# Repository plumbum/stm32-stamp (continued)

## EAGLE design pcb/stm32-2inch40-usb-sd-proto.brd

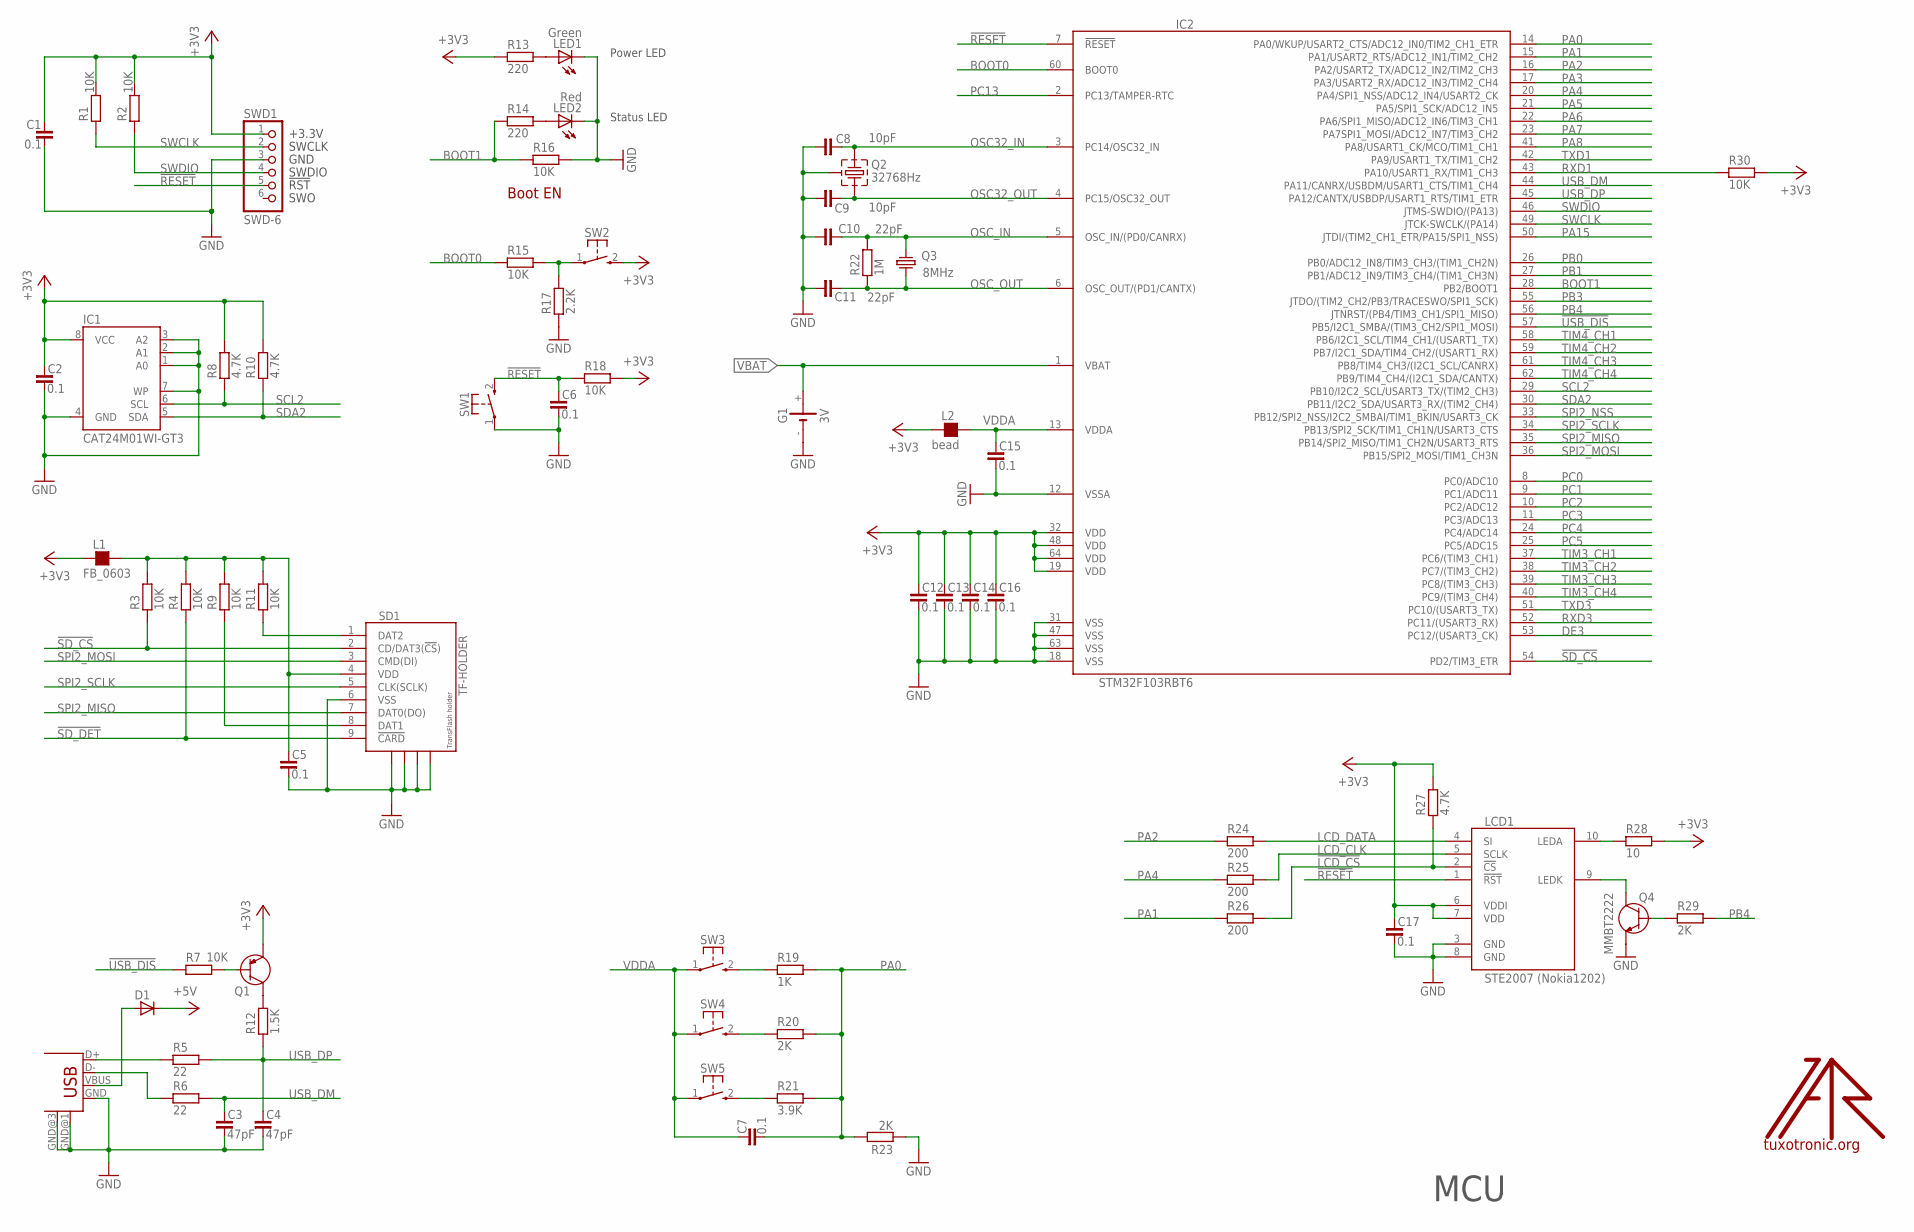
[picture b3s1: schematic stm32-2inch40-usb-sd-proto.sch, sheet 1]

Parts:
C1, C2, C5, C6, C7, C12, C13, C14, C15, C16, C17: 0.1; C0603
C3, C4: 47pF; C0603
C8, C9: 10pF; C0603
C10, C11: 22pF; C0603
D1: D-SOD-87; SOD87
G1: 3V; SMT1220
IC1: CAT24M01WI-GT3; SO08
IC2: STM32F103RBT6; TQFP64
L1: FB_0603; L0603
L2: bead; L0603
LCD1: STE2007 (Nokia1202); NOKIA1202LCD-EXT
LED1: Green; CHIP-LED0805
LED2: Red; CHIP-LED0805
LOGO1: LOGO; TT_LOGO
Q1: PNP-SOT23; SOT23
Q2: 32768Hz; TC38H-G
Q3: 8MHz; HC49/S
Q4: MMBT2222; SOT23
R1, R2, R3, R4, R7, R9, R11, R15, R16, R18, R30: 10K; R0603
R5, R6: 22; R0603
R8, R10, R27: 4.7K; R0603
R12: 1.5K; R0603
R13, R14: 220; R0603
R17: 2.2K; R0603
R19: 1K; R0603
R20, R23, R29: 2K; R0603
R21: 3.9K; R0603
R22: 1M; R0603
R24, R25, R26: 200; R0603
R28: 10; R0603
SD1: TF-HOLDER; TF-PULL
SW1, SW2, SW3, SW4, SW5: KSS-2EG4430
SWD1: SWD-6; JTAG6PIN
USB1: USB-MB-S

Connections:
!LCD_CS: LCD1.2 (!CS), R26.2, R27.1
!RESET: C6.1, IC2.7 (!RESET), LCD1.1 (!RST), R18.1, SW1.2 (S), SWD1.5
!SD_CS: IC2.54 (PD2/TIM3_ETR), R3.1, SD1.2 (CD/DAT3(!CS!))
!SD_DET: R4.1, SD1.9 (!CARD)
!USB_DIS: IC2.57 (PB5/I2C1_SMBA/(TIM3_CH2/SPI1_MOSI)), R7.1
+3V3: C1.1, C2.1, C12.1, C13.1, C14.1, C16.1, C17.1, IC1.8 (VCC), IC2.19 (VDD), IC2.32 (VDD), IC2.48 (VDD), IC2.64 (VDD), L1.1, L2.1, LCD1.6 (VDDI), LCD1.7 (VDD), Q1.2 (E), R1.2, R2.2, R8.2, R10.2, R13.1, R18.2, R27.2, R28.2, R30.2, SW2.2 (S), SWD1.1; also elsewhere on the board
+5V: D1.1 (C); also elsewhere on the board
BOOT0: IC2.60 (BOOT0), R15.1
BOOT1: IC2.28 (PB2/BOOT1), R14.1, R16.1
DE3: IC2.53 (PC12/(USART3_CK)); also elsewhere on the board
GND: C1.2, C2.2, C3.2, C4.2, C5.2, C6.2, C8.2, C9.2, C10.2, C11.2, C12.2, C13.2, C14.2, C15.2, C16.2, C17.2, G1.-, IC1.1 (A0), IC1.2 (A1), IC1.3 (A2), IC1.4 (GND), IC1.7 (WP), IC2.12 (VSSA), IC2.18 (VSS), IC2.31 (VSS), IC2.47 (VSS), IC2.63 (VSS), LCD1.3 (GND), LCD1.8 (GND), LED1.C, LED2.C, Q2.GND, Q4.2 (E), R16.2, R17.1, R23.1, SD1.6 (VSS), SD1.S1, SD1.S2, SD1.S3, SD1.S4, SW1.1, SWD1.3, USB1.GND, USB1.GND@1 (GND), USB1.GND@3 (GND); also elsewhere on the board
LCD_CLK: LCD1.5 (SCLK), R25.2
LCD_DATA: LCD1.4 (SI), R24.2
unnamed: Q1.3 (C), R12.2
unnamed: D1.2 (A), USB1.VBUS
unnamed: R15.2, R17.2, SW2.1
unnamed: C5.1, L1.2, R3.2, R4.2, R9.2, R11.2, SD1.4 (VDD)
unnamed: R11.1, SD1.1 (DAT2)
unnamed: R9.1, SD1.8 (DAT1)
unnamed: R5.1, USB1.D+
unnamed: LED1.A, R13.2
unnamed: LCD1.9 (LEDK), Q4.3 (C)
unnamed: LED2.A, R14.2
unnamed: LCD1.10 (LEDA), R28.1
unnamed: Q4.1 (B), R29.1
unnamed: R19.1, SW3.2 (S)
unnamed: R20.1, SW4.2 (S)
unnamed: R21.1, SW5.2 (S)
unnamed: R6.1, USB1.D-
unnamed: Q1.1 (B), R7.2
OSC32_IN: C8.1, IC2.3 (PC14/OSC32_IN), Q2.2
OSC32_OUT: C9.1, IC2.4 (PC15/OSC32_OUT), Q2.1
OSC_IN: C10.1, IC2.5 (OSC_IN/(PD0/CANRX)), Q3.1, R22.2
OSC_OUT: C11.1, IC2.6 (OSC_OUT/(PD1/CANTX)), Q3.2, R22.1
PA0: C7.2, IC2.14 (PA0/WKUP/USART2_CTS/ADC12_IN0/TIM2_CH1_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), R19.2, R20.2, R21.2, R23.2; also elsewhere on the board
PA1: IC2.15 (PA1/USART2_RTS/ADC12_IN1/TIM2_CH2), R26.1; also elsewhere on the board
PA2: IC2.16 (PA2/USART2_TX/ADC12_IN2/TIM2_CH3), R24.1; also elsewhere on the board
PA3: IC2.17 (PA3/USART2_RX/ADC12_IN3/TIM2_CH4); also elsewhere on the board
PA4: IC2.20 (PA4/SPI1_NSS/ADC12_IN4/USART2_CK), R25.1; also elsewhere on the board
PA5: IC2.21 (PA5/SPI1_SCK/ADC12_IN5); also elsewhere on the board
PA6: IC2.22 (PA6/SPI1_MISO/ADC12_IN6/TIM3_CH1); also elsewhere on the board
PA7: IC2.23 (PA7SPI1_MOSI/ADC12_IN7/TIM3_CH2); also elsewhere on the board
PA8: IC2.41 (PA8/USART1_CK/MCO/TIM1_CH1); also elsewhere on the board
PA15: IC2.50 (JTDI/(TIM2_CH1_ETR/PA15/SPI1_NSS)); also elsewhere on the board
PB0: IC2.26 (PB0/ADC12_IN8/TIM3_CH3/(TIM1_CH2N)); also elsewhere on the board
PB1: IC2.27 (PB1/ADC12_IN9/TIM3_CH4/(TIM1_CH3N)); also elsewhere on the board
PB3: IC2.55 (JTDO/(TIM2_CH2/PB3/TRACESWO/SPI1_SCK)); also elsewhere on the board
PB4: IC2.56 (JTNRST/(PB4/TIM3_CH1/SPI1_MISO)), R29.2
PC0: IC2.8 (PC0/ADC10); also elsewhere on the board
PC1: IC2.9 (PC1/ADC11); also elsewhere on the board
PC2: IC2.10 (PC2/ADC12); also elsewhere on the board
PC3: IC2.11 (PC3/ADC13); also elsewhere on the board
PC4: IC2.24 (PC4/ADC14); also elsewhere on the board
PC5: IC2.25 (PC5/ADC15); also elsewhere on the board
PC13: IC2.2 (PC13/TAMPER-RTC); also elsewhere on the board
RXD1: IC2.43 (PA10/USART1_RX/TIM1_CH3), R30.1; also elsewhere on the board
RXD3: IC2.52 (PC11/(USART3_RX)); also elsewhere on the board
SCL2: IC1.6 (SCL), IC2.29 (PB10/I2C2_SCL/USART3_TX/(TIM2_CH3)), R8.1; also elsewhere on the board
SDA2: IC1.5 (SDA), IC2.30 (PB11/I2C2_SDA/USART3_RX/(TIM2_CH4)), R10.1; also elsewhere on the board
SPI2_MISO: IC2.35 (PB14/SPI2_MISO/TIM1_CH2N/USART3_RTS), SD1.7 (DAT0(DO)); also elsewhere on the board
SPI2_MOSI: IC2.36 (PB15/SPI2_MOSI/TIM1_CH3N), SD1.3 (CMD(DI)); also elsewhere on the board
SPI2_NSS: IC2.33 (PB12/SPI2_NSS/I2C2_SMBAI/TIM1_BKIN/USAR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); also elsewhere on the board
SPI2_SCLK: IC2.34 (PB13/SPI2_SCK/TIM1_CH1N/USART3_CTS), SD1.5 (CLK(SCLK)); also elsewhere on the board
SWCLK: IC2.49 (JTCK-SWCLK/(PA14)), R1.1, SWD1.2
SWDIO: IC2.46 (JTMS-SWDIO/(PA13)), R2.1, SWD1.4
TIM3_CH1: IC2.37 (PC6/(TIM3_CH1)); also elsewhere on the board
TIM3_CH2: IC2.38 (PC7/(TIM3_CH2)); also elsewhere on the board
TIM3_CH3: IC2.39 (PC8/(TIM3_CH3)); also elsewhere on the board
TIM3_CH4: IC2.40 (PC9/(TIM3_CH4)); also elsewhere on the board
TIM4_CH1: IC2.58 (PB6/I2C1_SCL/TIM4_CH1/(USART1_TX)); also elsewhere on the board
TIM4_CH2: IC2.59 (PB7/I2C1_SDA/TIM4_CH2/(USART1_RX)); also elsewhere on the board
TIM4_CH3: IC2.61 (PB8/TIM4_CH3/(I2C1_SCL/CANRX)); also elsewhere on the board
TIM4_CH4: IC2.62 (PB9/TIM4_CH4/(I2C1_SDA/CANTX)); also elsewhere on the board
TXD1: IC2.42 (PA9/USART1_TX/TIM1_CH2); also elsewhere on the board
TXD3: IC2.51 (PC10/(USART3_TX)); also elsewhere on the board
USB_DM: C3.1, IC2.44 (PA11/CANRX/USBDM/USART1_CTS/TIM1_CH4), R6.2
USB_DP: C4.1, IC2.45 (PA12/CANTX/USBDP/USART1_RTS/TIM1_ETR), R5.2, R12.1
VBAT: G1.+, IC2.1 (VBAT)
VDDA: C7.1, C15.1, IC2.13 (VDDA), L2.2, SW3.1, SW4.1, SW5.1

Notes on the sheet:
Boot EN
Status LED
MCU
Power LED

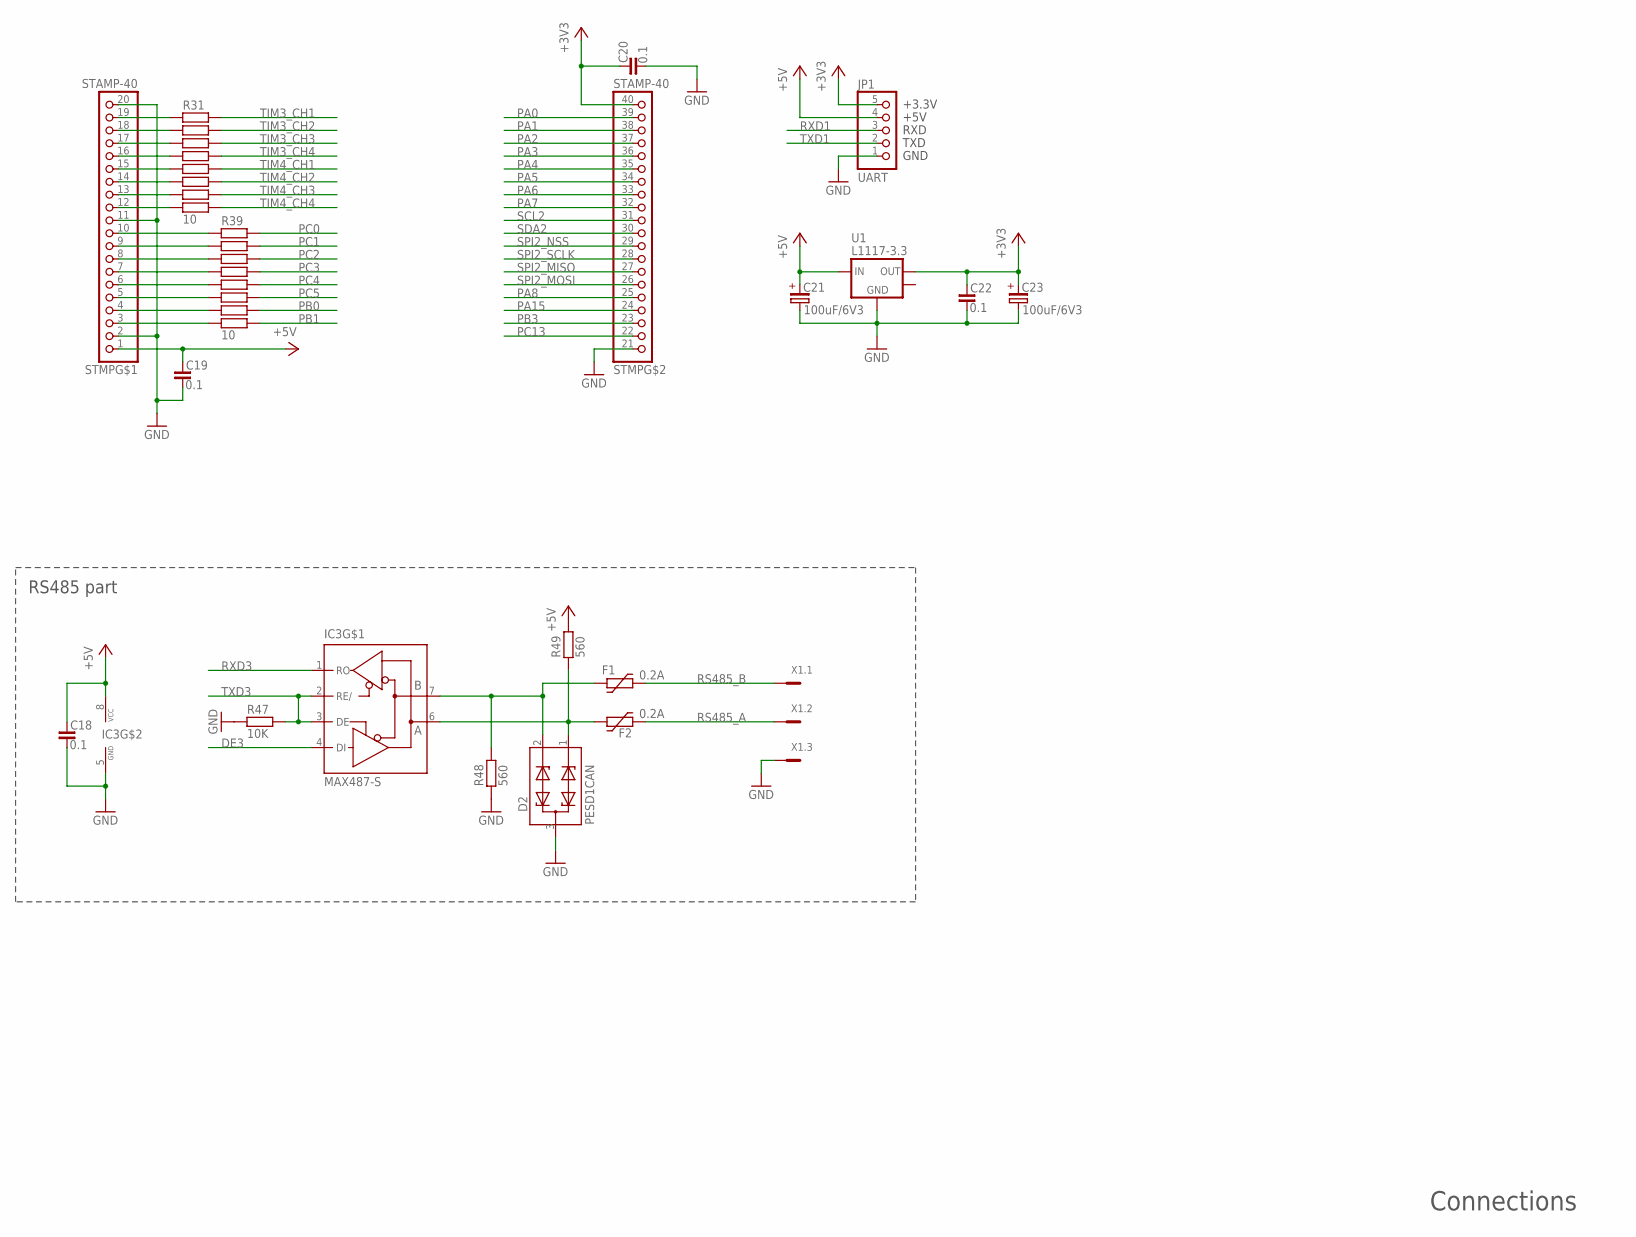
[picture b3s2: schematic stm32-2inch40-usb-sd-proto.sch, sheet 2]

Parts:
C18: 0.1; C0603
C19, C20, C22: 0.1; C0805
C21, C23: 100uF/6V3; SMC_D
D2: PESD1CAN; SOT23
F1, F2: 0.2A; 1206L
IC3: MAX487-S; SO08
JP1: UART; UART_1X05
R31, R32, R33, R34, R35, R36, R37, R38, R39, R40, R41, R42, R43, R44, R45, R46: 10; R0603
R47: 10K; R0603
R48, R49: 560; R0603
STMP: STAMP-40
U1: L1117-3.3; SOT223
X1: MCV3

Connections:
+3V3: C20.1, C22.1, C23.+, JP1.5, STMP.40 (20), U1.2 (OUT); also elsewhere on the board
+5V: C18.1, C19.1, C21.+, IC3.8 (VCC), JP1.4, R49.2, STMP.1, U1.3 (IN); also elsewhere on the board
DE3: IC3.4 (DI); also elsewhere on the board
GND: C18.2, C19.2, C20.2, C21.-, C22.2, C23.-, D2.3, IC3.5 (GND), JP1.1, R47.1, R48.1, STMP.2, STMP.11, STMP.20, STMP.21 (1), U1.1 (GND), X1.3; also elsewhere on the board
unnamed: D2.2, F1.P$1 (1), IC3.7 (B), R48.2
unnamed: R39.1, STMP.10
unnamed: R40.1, STMP.9
unnamed: R31.1, STMP.19
unnamed: R32.1, STMP.18
unnamed: R33.1, STMP.17
unnamed: R34.1, STMP.16
unnamed: R35.1, STMP.15
unnamed: R36.1, STMP.14
unnamed: R37.1, STMP.13
unnamed: R38.1, STMP.12
unnamed: R41.1, STMP.8
unnamed: R42.1, STMP.7
unnamed: R43.1, STMP.6
unnamed: R44.1, STMP.5
unnamed: R45.1, STMP.4
unnamed: R46.1, STMP.3
unnamed: D2.1, F2.P$1 (1), IC3.6 (A), R49.1
PA0: STMP.39 (19); also elsewhere on the board
PA1: STMP.38 (18); also elsewhere on the board
PA2: STMP.37 (17); also elsewhere on the board
PA3: STMP.36 (16); also elsewhere on the board
PA4: STMP.35 (15); also elsewhere on the board
PA5: STMP.34 (14); also elsewhere on the board
PA6: STMP.33 (13); also elsewhere on the board
PA7: STMP.32 (12); also elsewhere on the board
PA8: STMP.25 (5); also elsewhere on the board
PA15: STMP.24 (4); also elsewhere on the board
PB0: R45.2; also elsewhere on the board
PB1: R46.2; also elsewhere on the board
PB3: STMP.23 (3); also elsewhere on the board
PC0: R39.2; also elsewhere on the board
PC1: R40.2; also elsewhere on the board
PC2: R41.2; also elsewhere on the board
PC3: R42.2; also elsewhere on the board
PC4: R43.2; also elsewhere on the board
PC5: R44.2; also elsewhere on the board
PC13: STMP.22 (2); also elsewhere on the board
RS485_A: F2.P$2 (2), X1.2
RS485_B: F1.P$2 (2), X1.1
RXD1: JP1.3; also elsewhere on the board
RXD3: IC3.1 (RO); also elsewhere on the board
SCL2: STMP.31 (11); also elsewhere on the board
SDA2: STMP.30 (10); also elsewhere on the board
SPI2_MISO: STMP.27 (7); also elsewhere on the board
SPI2_MOSI: STMP.26 (6); also elsewhere on the board
SPI2_NSS: STMP.29 (9); also elsewhere on the board
SPI2_SCLK: STMP.28 (8); also elsewhere on the board
TIM3_CH1: R31.2; also elsewhere on the board
TIM3_CH2: R32.2; also elsewhere on the board
TIM3_CH3: R33.2; also elsewhere on the board
TIM3_CH4: R34.2; also elsewhere on the board
TIM4_CH1: R35.2; also elsewhere on the board
TIM4_CH2: R36.2; also elsewhere on the board
TIM4_CH3: R37.2; also elsewhere on the board
TIM4_CH4: R38.2; also elsewhere on the board
TXD1: JP1.2; also elsewhere on the board
TXD3: IC3.2 (RE/), IC3.3 (DE), R47.2; also elsewhere on the board

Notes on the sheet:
Connections
RS485 part

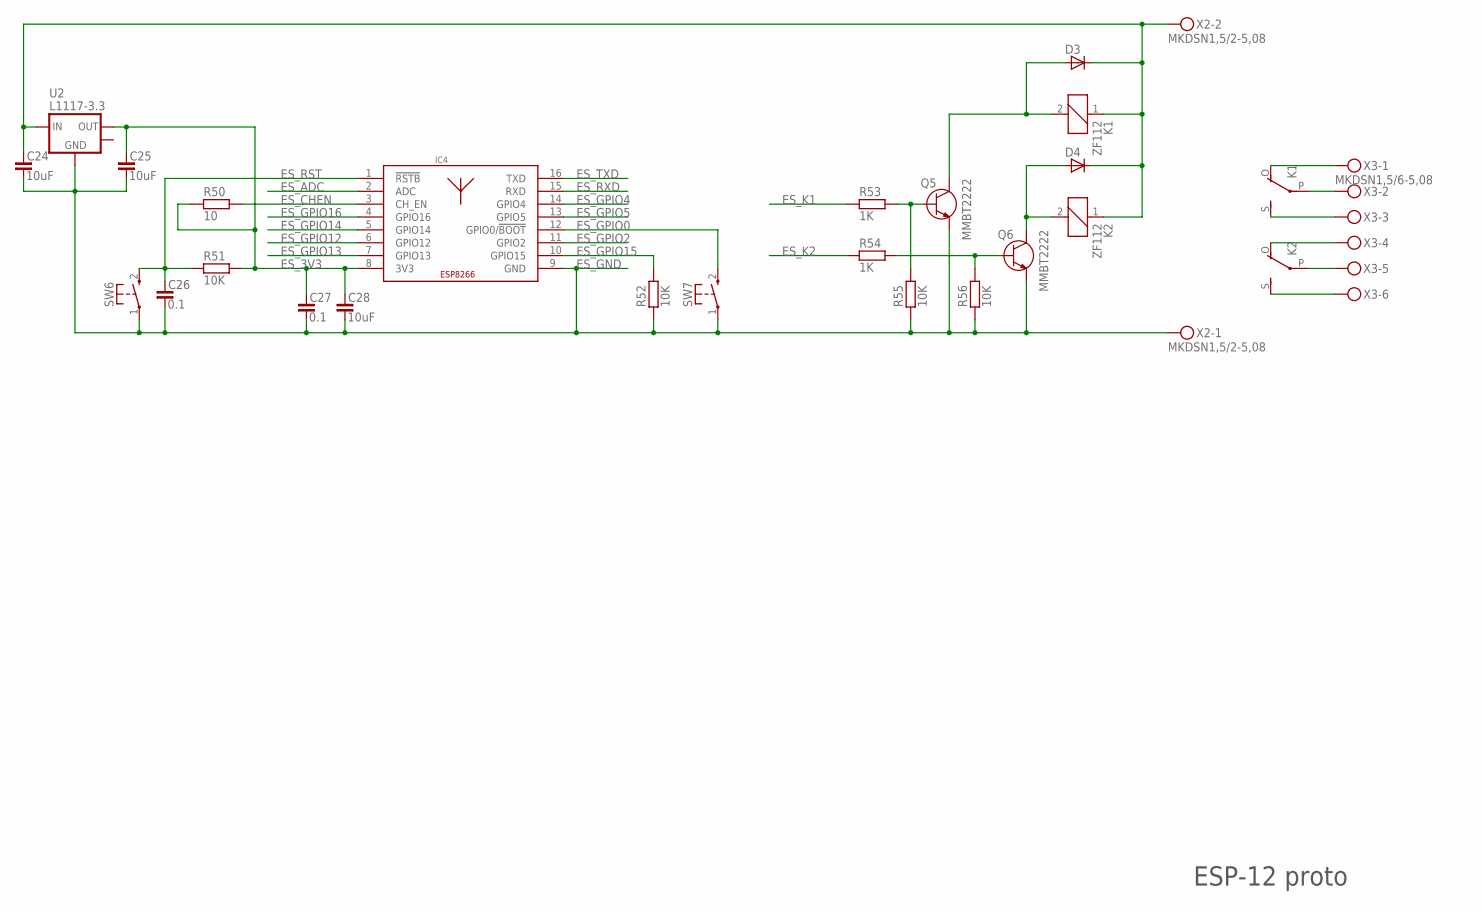
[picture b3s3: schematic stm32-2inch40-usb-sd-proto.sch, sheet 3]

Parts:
C24, C25, C28: 10uF; C0805
C26, C27: 0.1; C0805
D3, D4: D-SOD-80; SOD80
IC4: ESP-12; ESP12
K1, K2: ZF112
Q5, Q6: MMBT2222; SOT23
R50: 10; R0805
R51, R52, R55, R56: 10K; R0805
R53, R54: 1K; R0805
SW6, SW7: KSS-2EG4430
U2: L1117-3.3; SOT223
X2: MKDSN1,5/2-5,08
X3: MKDSN1,5/6-5,08

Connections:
+5V1: C24.1, D3.1 (C), D4.1 (C), K1.1, K2.1, U2.3 (IN), X2.2
ES_3V3: C25.1, C27.1, C28.1, IC4.8 (3V3), R50.1, R51.2, U2.2 (OUT)
ES_ADC: IC4.2 (ADC)
ES_CHEN: IC4.3 (CH_EN), R50.2
ES_GND: C24.2, C25.2, C26.2, C27.2, C28.2, IC4.9 (GND), Q5.2 (E), Q6.2 (E), R52.1, R55.1, R56.1, SW6.1, SW7.1, U2.1 (GND), X2.1
ES_GPIO0: IC4.12 (GPIO0/!BOOT), SW7.2 (S)
ES_GPIO2: IC4.11 (GPIO2)
ES_GPIO4: IC4.14 (GPIO4)
ES_GPIO5: IC4.13 (GPIO5)
ES_GPIO12: IC4.6 (GPIO12)
ES_GPIO13: IC4.7 (GPIO13)
ES_GPIO14: IC4.5 (GPIO14)
ES_GPIO15: IC4.10 (GPIO15), R52.2
ES_GPIO16: IC4.4 (GPIO16)
ES_K1: R53.1
ES_K2: R54.1
ES_RST: C26.1, IC4.1 (!RSTB), R51.1, SW6.2 (S)
ES_RXD: IC4.15 (RXD)
ES_TXD: IC4.16 (TXD)
unnamed: Q6.1 (B), R54.2, R56.2
unnamed: D4.2 (A), K2.2, Q6.3 (C)
unnamed: D3.2 (A), K1.2, Q5.3 (C)
unnamed: Q5.1 (B), R53.2, R55.2
unnamed: K1.O, X3.1
unnamed: K1.P, X3.2
unnamed: K1.S, X3.3
unnamed: K2.O, X3.4
unnamed: K2.P, X3.5
unnamed: K2.S, X3.6

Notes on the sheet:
ESP-12 proto

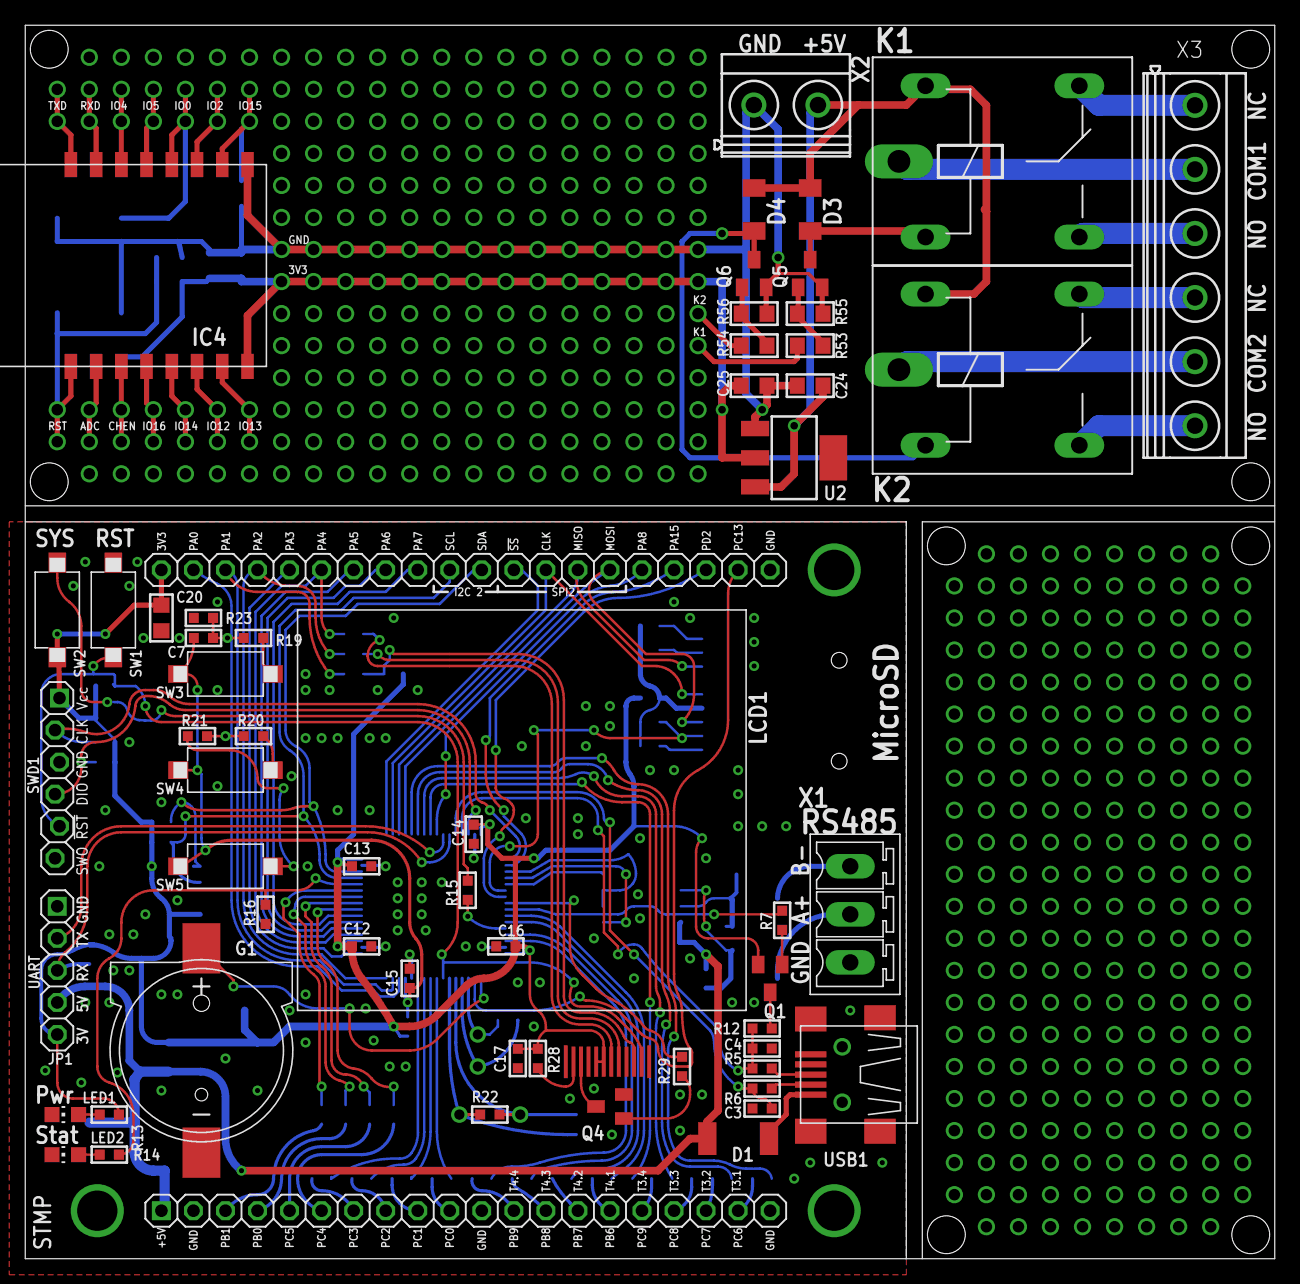
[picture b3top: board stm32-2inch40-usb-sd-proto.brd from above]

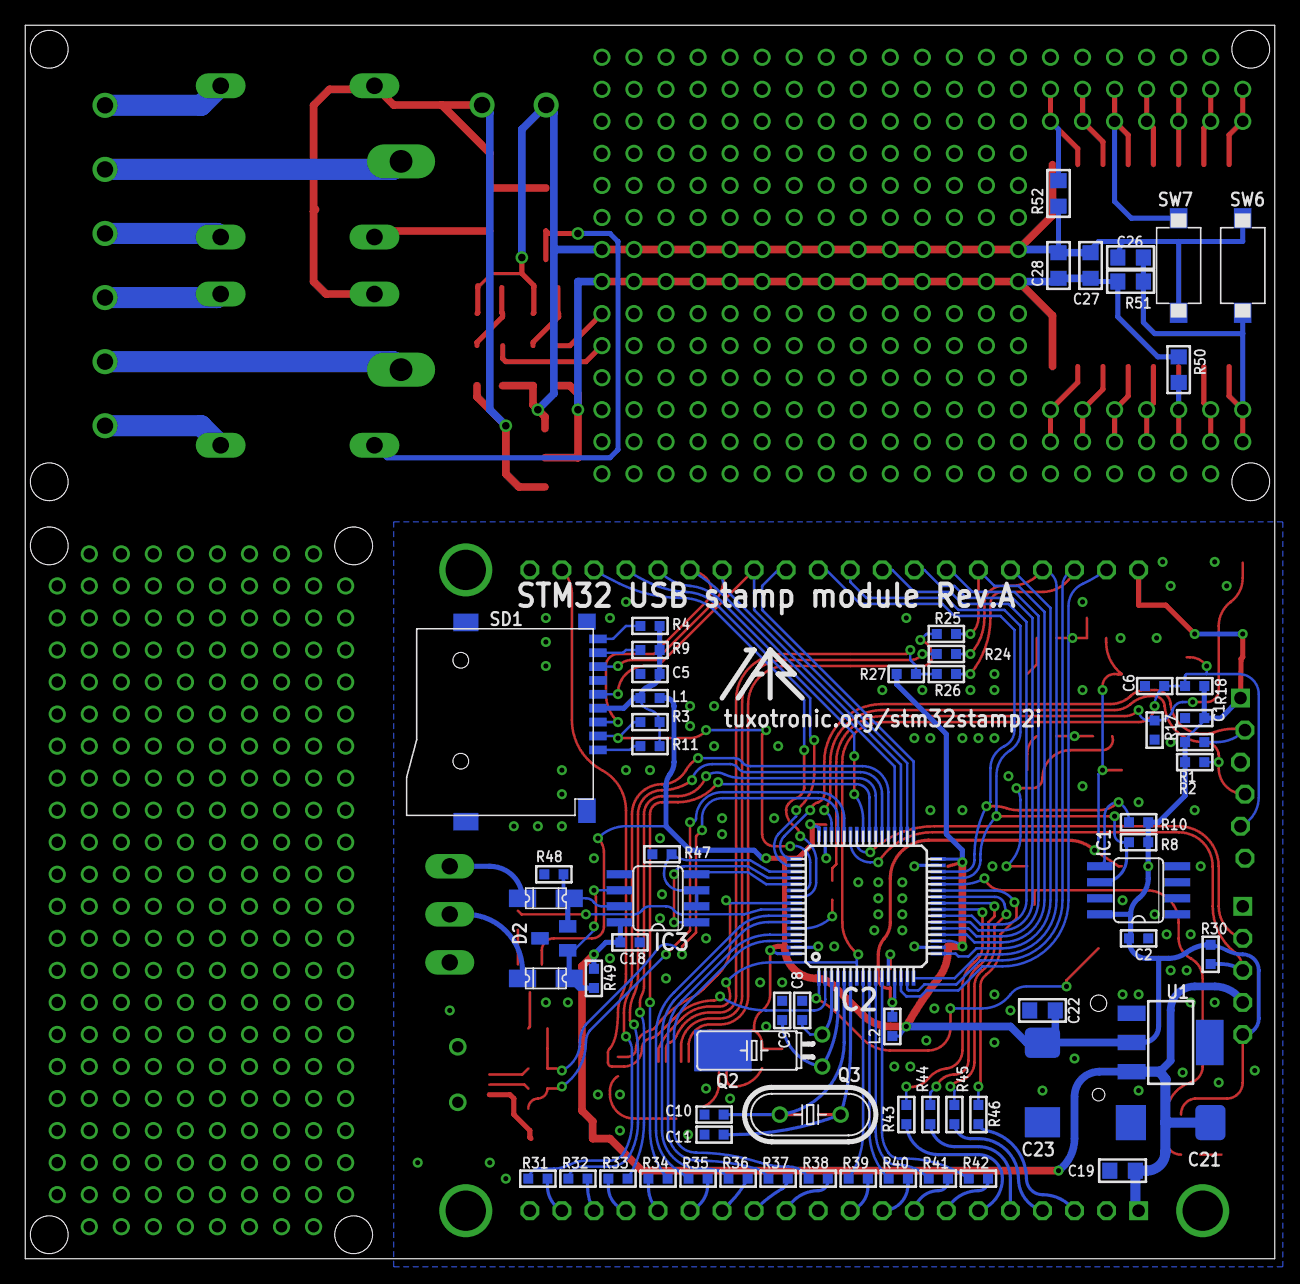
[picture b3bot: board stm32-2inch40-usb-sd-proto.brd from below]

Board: 2 copper layers, 99.1 x 97.8 mm, 126 parts (68 on the bottom side), 116 nets.

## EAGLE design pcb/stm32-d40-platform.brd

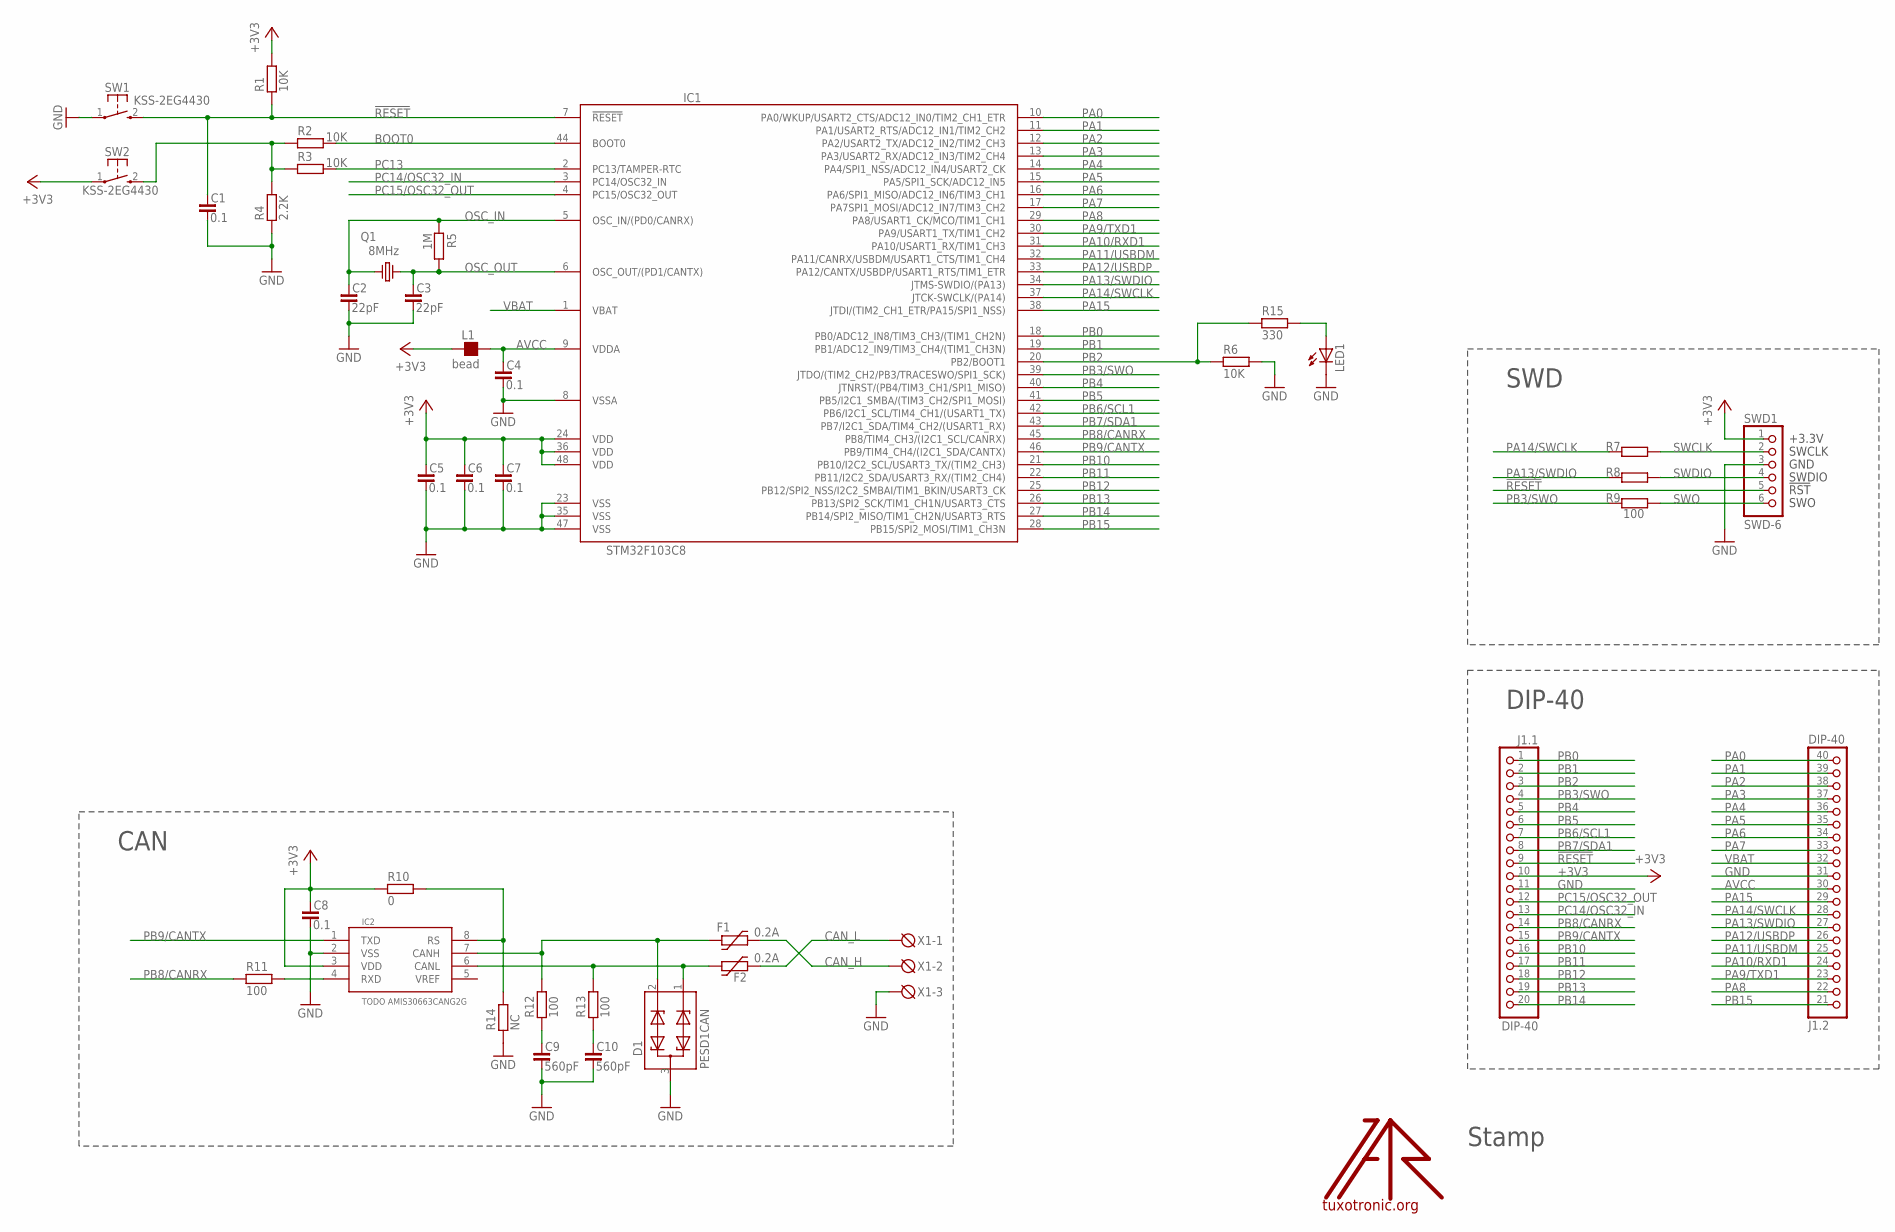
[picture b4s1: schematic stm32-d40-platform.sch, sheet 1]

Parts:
C1, C4, C5, C6, C7, C8: 0.1; C0603
C2, C3: 22pF; C0603
C9, C10: 560pF; C0603
D1: PESD1CAN; SOT23
F1, F2: 0.2A; 1206L
IC1: STM32F103C8; LQFP48
IC2: TODO AMIS30663CANG2G; SO08
J1: DIP-40
L1: bead; L0603
LED1: LEDCHIPLED_0603; CHIPLED_0603
Q1: 8MHz; HC49/S
R1, R2, R3, R6: 10K; R0603
R4: 2.2K; R0603
R5: 1M; R0603
R7, R8, R9, R11, R12, R13: 100; R0603
R10: 0; R0603
R14: NC; R0603
R15: 330; R0603
SW1, SW2: KSS-2EG4430
SWD1: SWD-6; JTAG6PIN
U$: LOGO; TT_LOGO
X1: DG3XX-03-3.5; DG350-3.5-03P

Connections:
!RESET: C1.1, IC1.7 (!RESET), J1.9, R1.1, SW1.2 (S), SWD1.5; also elsewhere on the board
+3V3: C5.1, C6.1, C7.1, C8.1, IC1.24 (VDD), IC1.36 (VDD), IC1.48 (VDD), IC2.3 (VDD), J1.10, L1.1, R1.2, R10.1, SW2.1, SWD1.1; also elsewhere on the board
AVCC: C4.1, IC1.9 (VDDA), J1.30 (10), L1.2
BOOT0: IC1.44 (BOOT0), R2.2
CAN_CTRL: IC2.8 (RS), R10.2, R14.2
CAN_H: F1.P$2 (2), X1.2
CAN_L: F2.P$2 (2), X1.1
GND: C1.2, C2.2, C3.2, C4.2, C5.2, C6.2, C7.2, C8.2, C9.2, C10.2, D1.3, IC1.8 (VSSA), IC1.23 (VSS), IC1.35 (VSS), IC1.47 (VSS), IC2.2 (VSS), J1.11, J1.31 (11), LED1.C, R4.1, R6.2, R14.1, SW1.1, SWD1.3, X1.3; also elsewhere on the board
unnamed: R2.1, R3.1, R4.2, SW2.2 (S)
unnamed: LED1.A, R15.2
unnamed: IC2.4 (RXD), R11.2
unnamed: D1.2, F1.P$1 (1), IC2.7 (CANH), R12.2
unnamed: D1.1, F2.P$1 (1), IC2.6 (CANL), R13.2
unnamed: C10.1, R13.1
unnamed: C9.1, R12.1
OSC_IN: C2.1, IC1.5 (OSC_IN/(PD0/CANRX)), Q1.1, R5.1
OSC_OUT: C3.1, IC1.6 (OSC_OUT/(PD1/CANTX)), Q1.2, R5.2
PA0: IC1.10 (PA0/WKUP/USART2_CTS/ADC12_IN0/TIM2_CH1_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), J1.40 (20)
PA1: IC1.11 (PA1/USART2_RTS/ADC12_IN1/TIM2_CH2), J1.39 (19)
PA2: IC1.12 (PA2/USART2_TX/ADC12_IN2/TIM2_CH3), J1.38 (18)
PA3: IC1.13 (PA3/USART2_RX/ADC12_IN3/TIM2_CH4), J1.37 (17)
PA4: IC1.14 (PA4/SPI1_NSS/ADC12_IN4/USART2_CK), J1.36 (16)
PA5: IC1.15 (PA5/SPI1_SCK/ADC12_IN5), J1.35 (15)
PA6: IC1.16 (PA6/SPI1_MISO/ADC12_IN6/TIM3_CH1), J1.34 (14)
PA7: IC1.17 (PA7SPI1_MOSI/ADC12_IN7/TIM3_CH2), J1.33 (13)
PA8: IC1.29 (PA8/USART1_CK/MCO/TIM1_CH1), J1.22 (2)
PA9/TXD1: IC1.30 (PA9/USART1_TX/TIM1_CH2), J1.23 (3)
PA10/RXD1: IC1.31 (PA10/USART1_RX/TIM1_CH3), J1.24 (4)
PA11/USBDM: IC1.32 (PA11/CANRX/USBDM/USART1_CTS/TIM1_CH4), J1.25 (5)
PA12/USBDP: IC1.33 (PA12/CANTX/USBDP/USART1_RTS/TIM1_ETR), J1.26 (6)
PA13/SWDIO: IC1.34 (JTMS-SWDIO/(PA13)), J1.27 (7), R8.1
PA14/SWCLK: IC1.37 (JTCK-SWCLK/(PA14)), J1.28 (8), R7.1
PA15: IC1.38 (JTDI/(TIM2_CH1_ETR/PA15/SPI1_NSS)), J1.29 (9)
PB0: IC1.18 (PB0/ADC12_IN8/TIM3_CH3/(TIM1_CH2N)), J1.1
PB1: IC1.19 (PB1/ADC12_IN9/TIM3_CH4/(TIM1_CH3N)), J1.2
PB2: IC1.20 (PB2/BOOT1), J1.3, R6.1, R15.1
PB3/SWO: IC1.39 (JTDO/(TIM2_CH2/PB3/TRACESWO/SPI1_SCK)), J1.4, R9.1
PB4: IC1.40 (JTNRST/(PB4/TIM3_CH1/SPI1_MISO)), J1.5
PB5: IC1.41 (PB5/I2C1_SMBA/(TIM3_CH2/SPI1_MOSI)), J1.6
PB6/SCL1: IC1.42 (PB6/I2C1_SCL/TIM4_CH1/(USART1_TX)), J1.7
PB7/SDA1: IC1.43 (PB7/I2C1_SDA/TIM4_CH2/(USART1_RX)), J1.8
PB8/CANRX: IC1.45 (PB8/TIM4_CH3/(I2C1_SCL/CANRX)), J1.14, R11.1
PB9/CANTX: IC1.46 (PB9/TIM4_CH4/(I2C1_SDA/CANTX)), IC2.1 (TXD), J1.15
PB10: IC1.21 (PB10/I2C2_SCL/USART3_TX/(TIM2_CH3)), J1.16
PB11: IC1.22 (PB11/I2C2_SDA/USART3_RX/(TIM2_CH4)), J1.17
PB12: IC1.25 (PB12/SPI2_NSS/I2C2_SMBAI/TIM1_BKIN/USAR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), J1.18
PB13: IC1.26 (PB13/SPI2_SCK/TIM1_CH1N/USART3_CTS), J1.19
PB14: IC1.27 (PB14/SPI2_MISO/TIM1_CH2N/USART3_RTS), J1.20
PB15: IC1.28 (PB15/SPI2_MOSI/TIM1_CH3N), J1.21 (1)
PC13: IC1.2 (PC13/TAMPER-RTC), R3.2
PC14/OSC32_IN: IC1.3 (PC14/OSC32_IN), J1.13
PC15/OSC32_OUT: IC1.4 (PC15/OSC32_OUT), J1.12
SWCLK: R7.2, SWD1.2; also elsewhere on the board
SWDIO: R8.2, SWD1.4; also elsewhere on the board
SWO: R9.2, SWD1.6; also elsewhere on the board
VBAT: IC1.1 (VBAT), J1.32 (12)

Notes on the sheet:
CAN
DIP-40
SWD
Stamp
